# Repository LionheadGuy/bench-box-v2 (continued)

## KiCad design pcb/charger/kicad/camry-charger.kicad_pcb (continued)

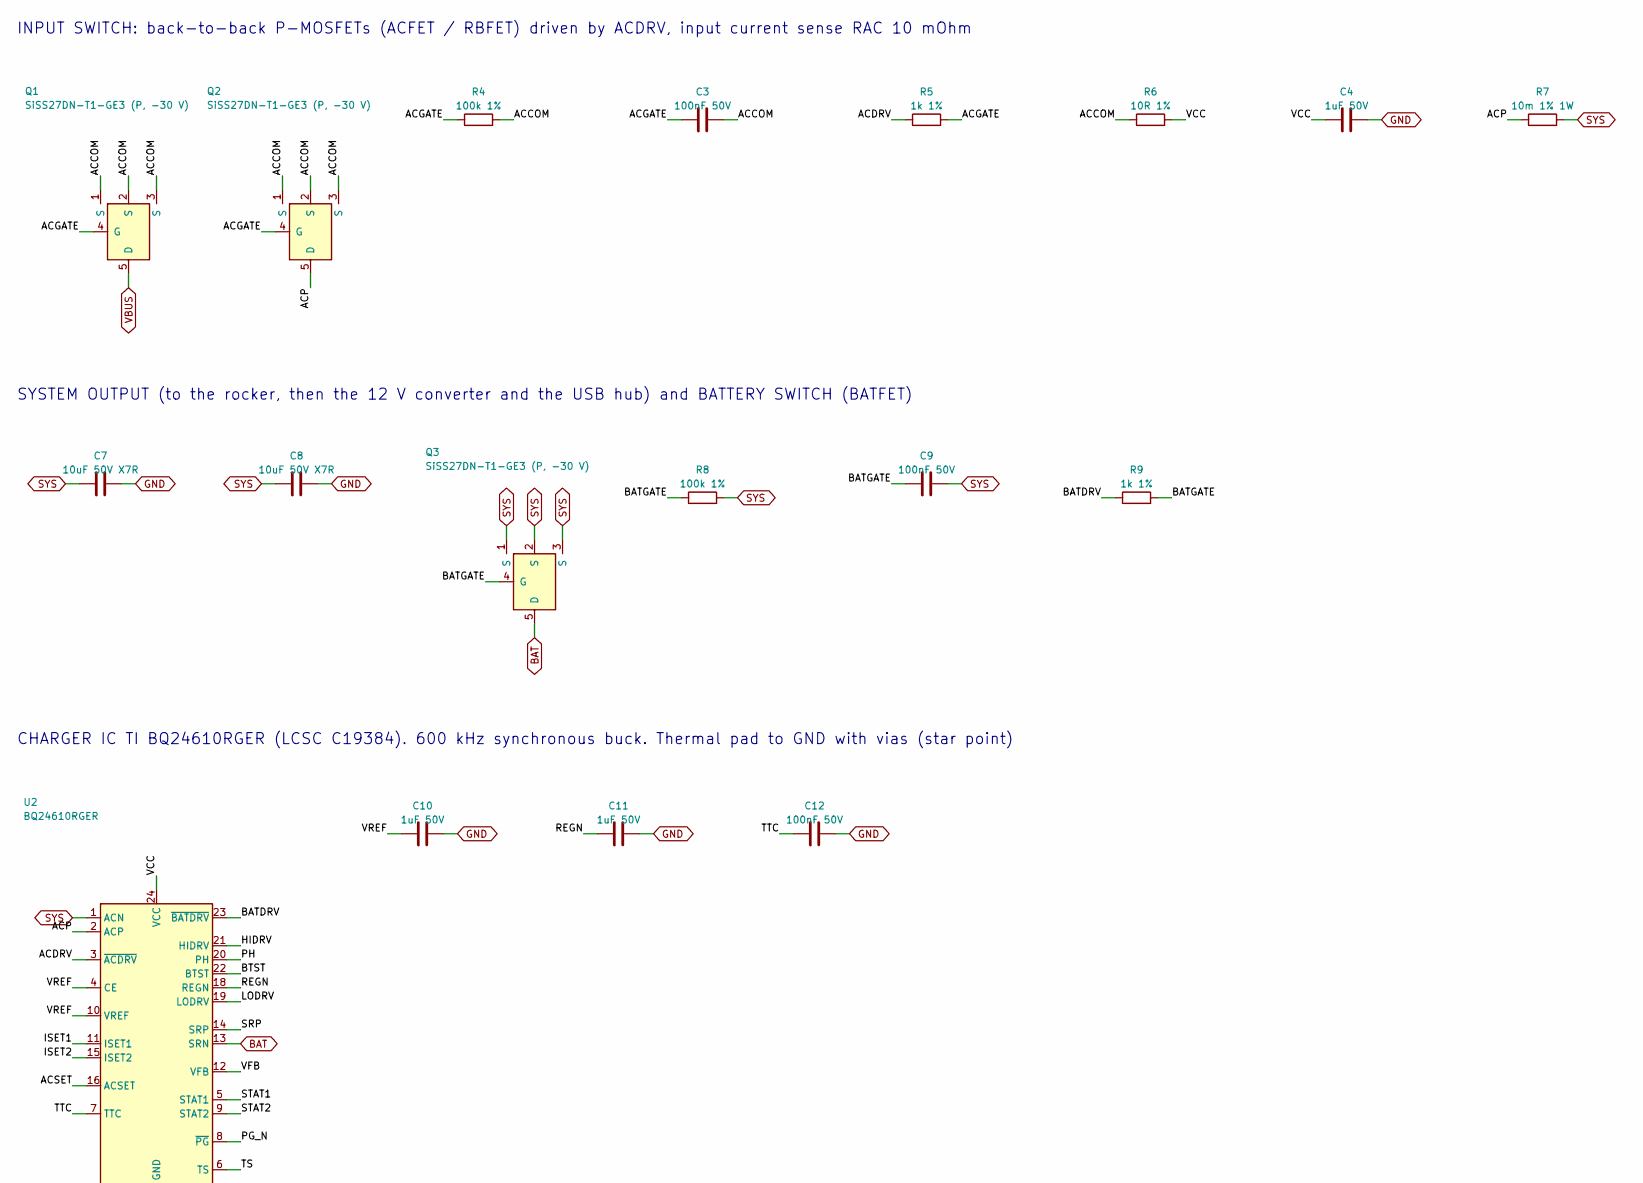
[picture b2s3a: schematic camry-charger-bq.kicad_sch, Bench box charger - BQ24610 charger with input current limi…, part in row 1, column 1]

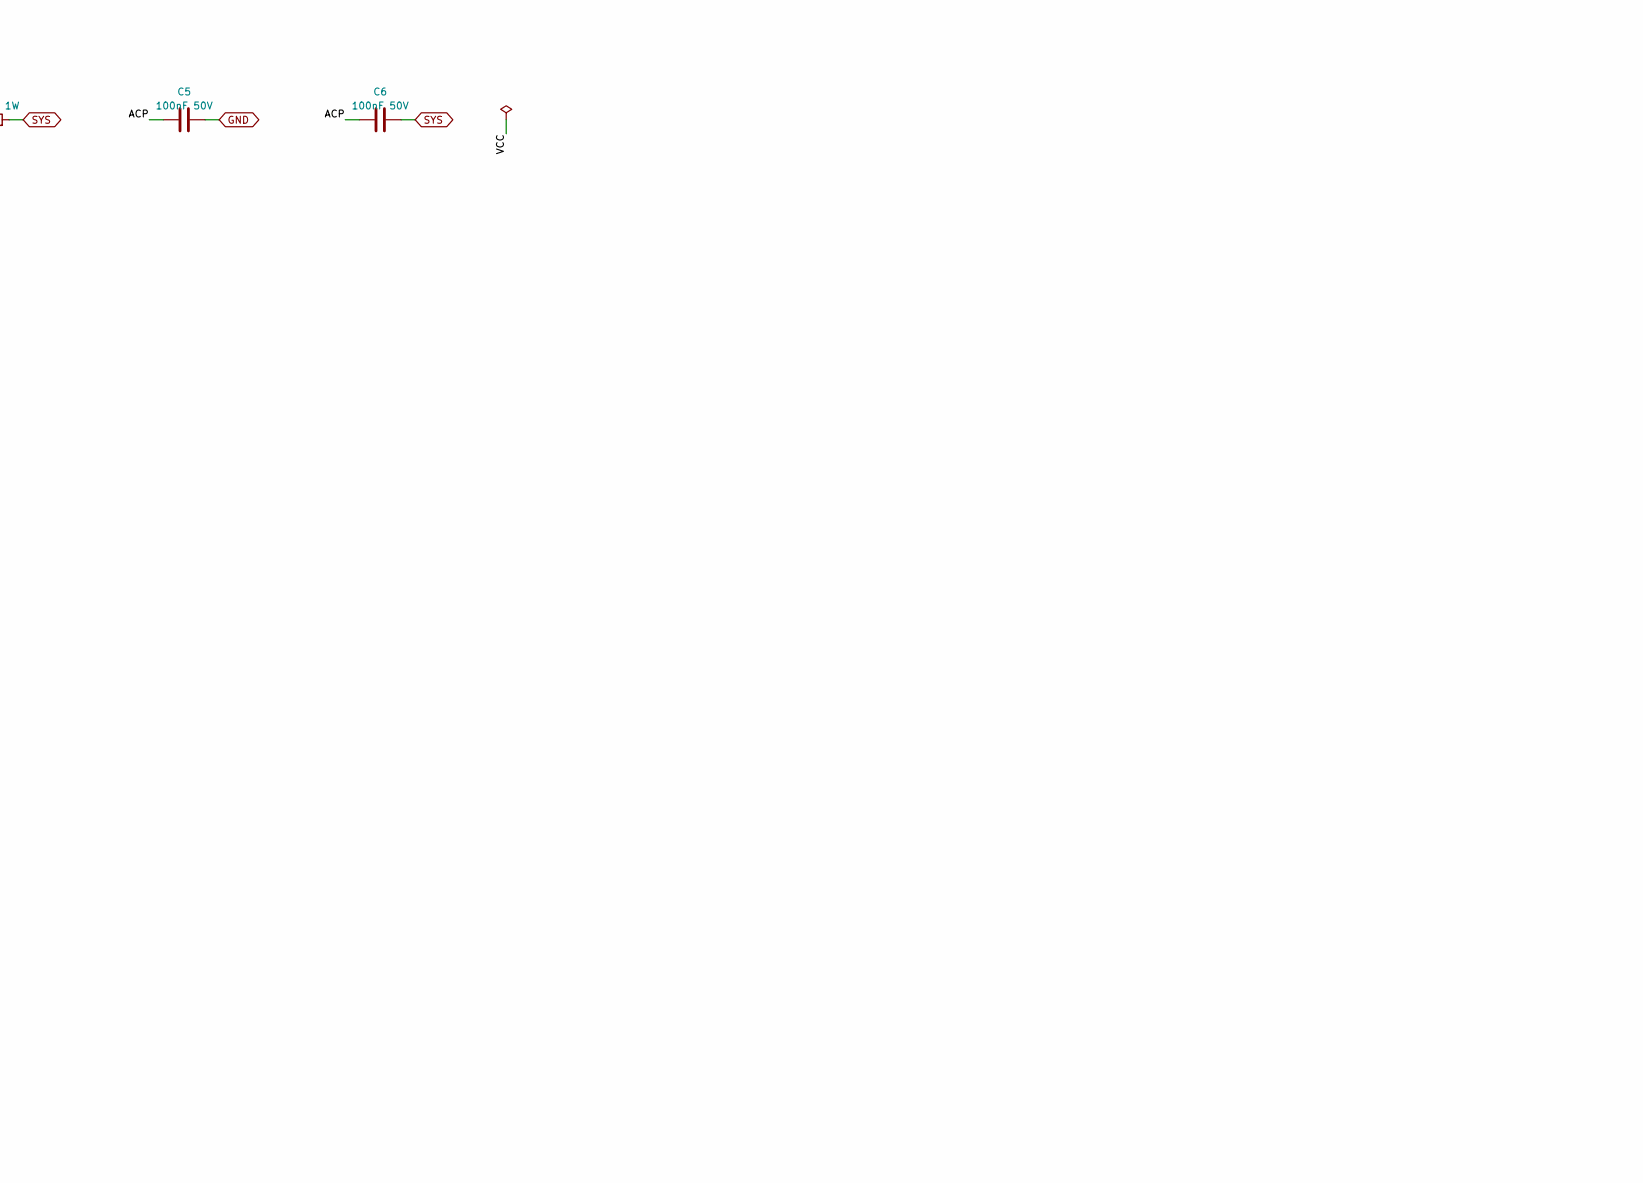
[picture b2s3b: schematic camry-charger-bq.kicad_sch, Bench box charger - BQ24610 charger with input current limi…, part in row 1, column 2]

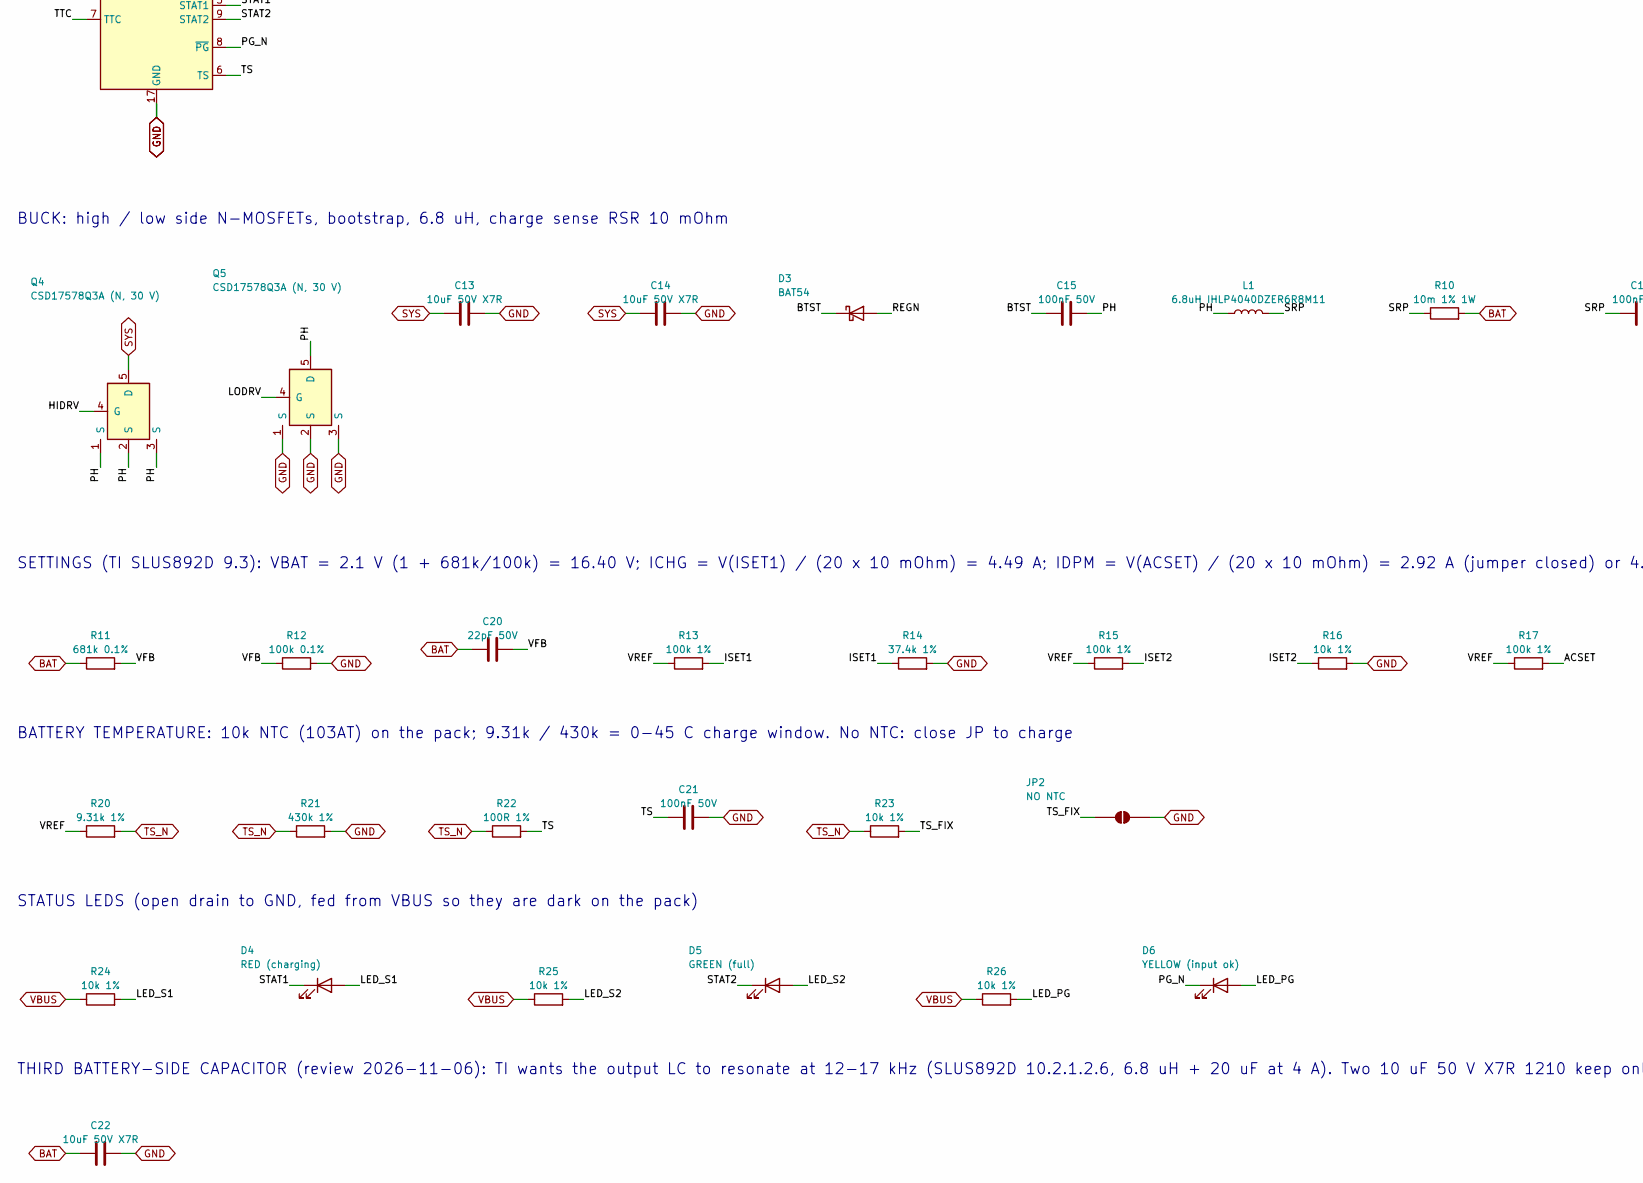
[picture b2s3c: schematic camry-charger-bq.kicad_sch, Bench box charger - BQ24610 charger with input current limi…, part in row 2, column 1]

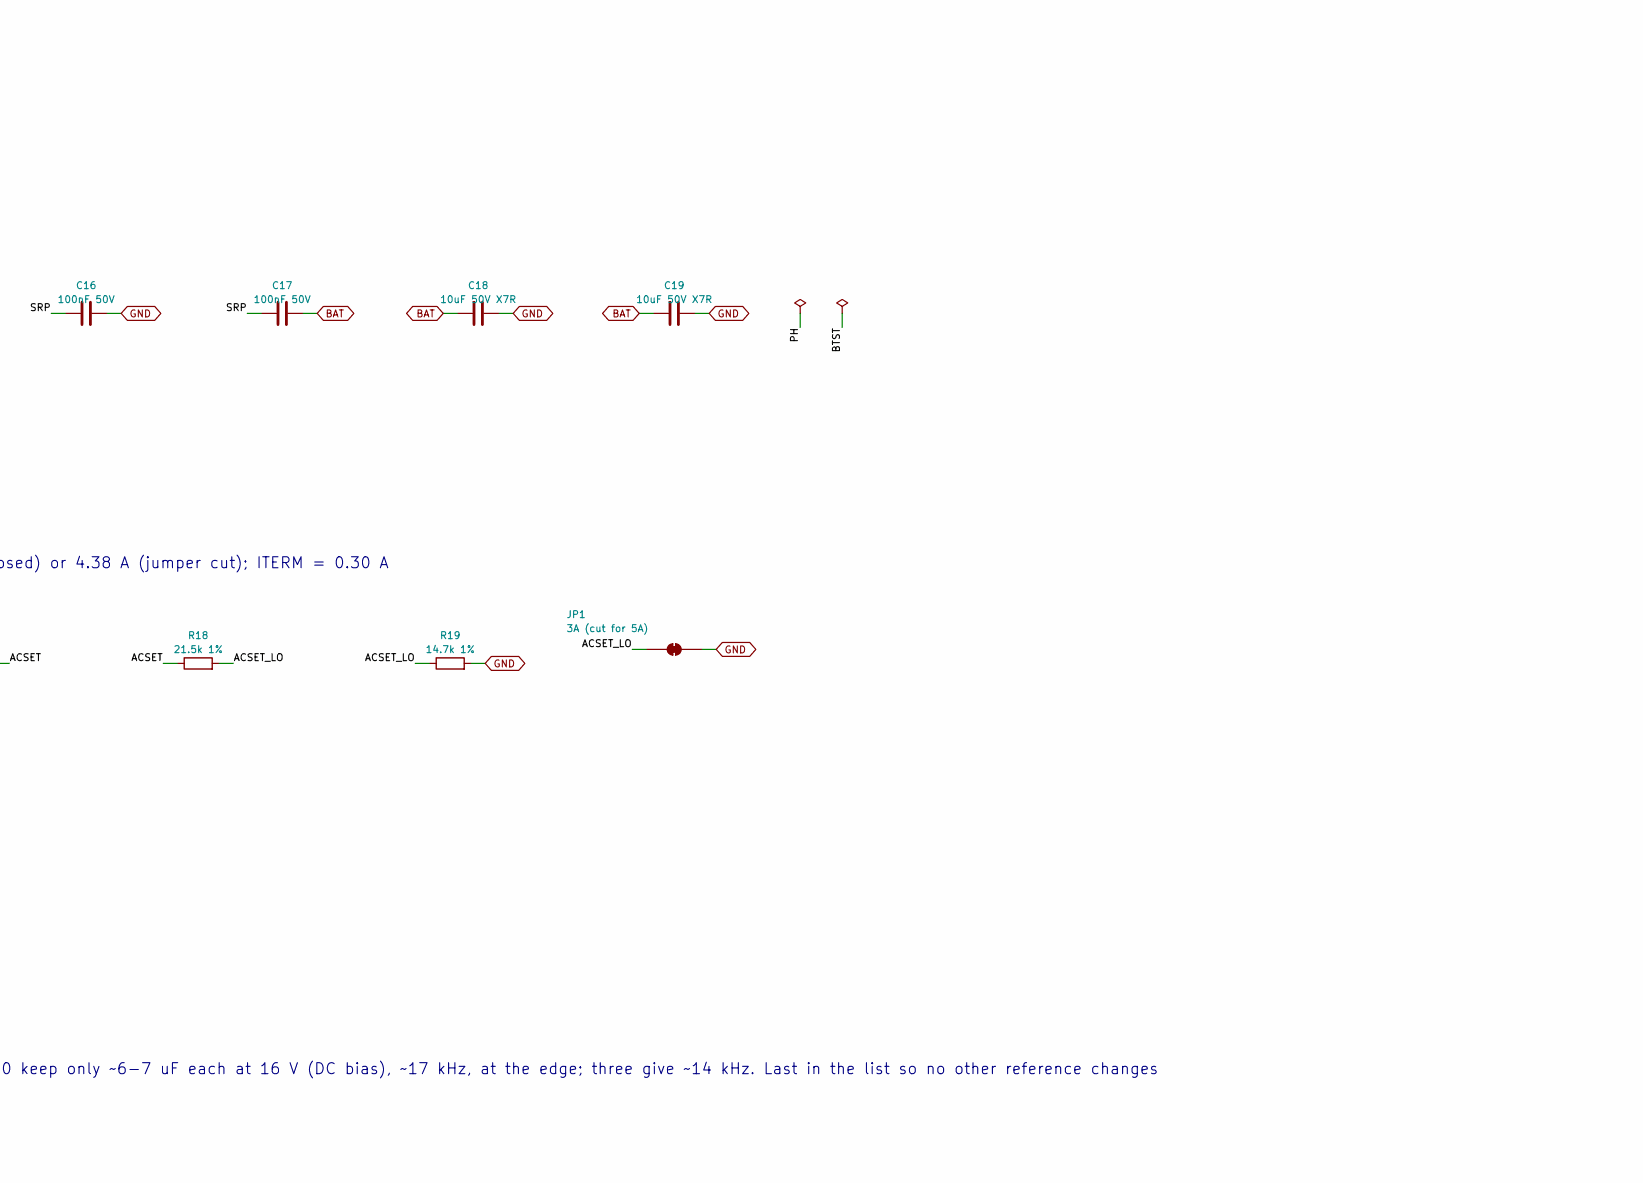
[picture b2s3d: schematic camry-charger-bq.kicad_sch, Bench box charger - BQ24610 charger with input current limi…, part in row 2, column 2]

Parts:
C3, C5, C6, C9, C12, C15, C16, C17, C21: 100nF 50V; C_0603_1608Metric; MPN GRM188R71H104KA93D
C4, C10, C11: 1uF 50V; C_0805_2012Metric; MPN GRM21BR71H105KA12L
C7, C8, C13, C14, C18, C19, C22: 10uF 50V X7R; C_1210_3225Metric; MPN GRM32ER71H106KA12L
C20: 22pF 50V; C_0603_1608Metric; MPN GRM1885C1H220JA01D
D3: BAT54; D_SOD-323; MPN BAT54WS-7-F
D4: RED (charging); LED_0603_1608Metric; MPN LTST-C191KRKT
D5: GREEN (full); LED_0603_1608Metric; MPN LTST-C191KGKT
D6: YELLOW (input ok); LED_0603_1608Metric; MPN LTST-C191KSKT
JP1: 3A (cut for 5A); SolderJumper-2_P1.3mm_Bridged_RoundedPad1.0x1.5mm
JP2: NO NTC; SolderJumper-2_P1.3mm_Open_RoundedPad1.0x1.5mm
L1: 6.8uH IHLP4040DZER6R8M11; L_Vishay_IHLP-4040; MPN IHLP4040DZER6R8M11
Q1, Q2, Q3: SiSS27DN-T1-GE3 (P, -30 V); Vishay_PowerPAK_1212-8_Single; MPN SISS27DN-T1-GE3
Q4, Q5: CSD17578Q3A (N, 30 V); VSON-8_3.3x3.3mm_P0.65mm_NexFET; MPN CSD17578Q3A; LCSC C205986
R4, R8, R13, R15, R17: 100k 1%; R_0603_1608Metric; MPN RC0603FR-07100KL
R5, R9: 1k 1%; R_0603_1608Metric; MPN RC0603FR-071KL
R6: 10R 1%; R_1206_3216Metric; MPN RC1206FR-0710RL
R7, R10: 10m 1% 1W; R_2512_6332Metric; MPN WSL2512R0100FEA
R11: 681k 0.1%; R_0603_1608Metric; MPN ERA-3AEB6813V
R12: 100k 0.1%; R_0603_1608Metric; MPN ERA-3AEB104V
R14: 37.4k 1%; R_0603_1608Metric; MPN RC0603FR-0737K4L
R16, R23, R24, R25, R26: 10k 1%; R_0603_1608Metric; MPN RC0603FR-0710KL
R18: 21.5k 1%; R_0603_1608Metric; MPN RC0603FR-0721K5L
R19: 14.7k 1%; R_0603_1608Metric; MPN RC0603FR-0714K7L
R20: 9.31k 1%; R_0603_1608Metric; MPN RC0603FR-079K31L
R21: 430k 1%; R_0603_1608Metric; MPN RC0603FR-07430KL
R22: 100R 1%; R_0603_1608Metric; MPN RC0603FR-07100RL
U2: BQ24610RGER; VQFN-24-1EP_4x4mm_P0.5mm_EP2.45x2.45mm_ThermalVias; MPN BQ24610RGER; LCSC C19384

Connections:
/BQ24610 charger with input current limiting and power path/ACCOM: C3.2, Q1.1 (S), Q1.2 (S), Q1.3 (S), Q2.1 (S), Q2.2 (S), Q2.3 (S), R4.2, R6.1
/BQ24610 charger with input current limiting and power path/ACDRV: R5.1, U2.3 (~ACDRV)
/BQ24610 charger with input current limiting and power path/ACGATE: C3.1, Q1.4 (G), Q2.4 (G), R4.1, R5.2
/BQ24610 charger with input current limiting and power path/ACP: C5.1, C6.1, Q2.5 (D), R7.1, U2.2 (ACP)
/BQ24610 charger with input current limiting and power path/ACSET: R17.2, R18.1, U2.16 (ACSET)
/BQ24610 charger with input current limiting and power path/ACSET_LO: JP1.1 (A), R18.2, R19.1
/BQ24610 charger with input current limiting and power path/BATDRV: R9.1, U2.23 (~BATDRV)
/BQ24610 charger with input current limiting and power path/BATGATE: C9.1, Q3.4 (G), R8.1, R9.2
/BQ24610 charger with input current limiting and power path/BTST: C15.1, D3.1 (K), U2.22 (BTST)
/BQ24610 charger with input current limiting and power path/HIDRV: Q4.4 (G), U2.21 (HIDRV)
/BQ24610 charger with input current limiting and power path/ISET1: R13.2, R14.1, U2.11 (ISET1)
/BQ24610 charger with input current limiting and power path/ISET2: R15.2, R16.1, U2.15 (ISET2)
/BQ24610 charger with input current limiting and power path/LED_PG: D6.2 (A), R26.2
/BQ24610 charger with input current limiting and power path/LED_S1: D4.2 (A), R24.2
/BQ24610 charger with input current limiting and power path/LED_S2: D5.2 (A), R25.2
/BQ24610 charger with input current limiting and power path/LODRV: Q5.4 (G), U2.19 (LODRV)
/BQ24610 charger with input current limiting and power path/PG_N: D6.1 (K), U2.8 (~PG)
/BQ24610 charger with input current limiting and power path/PH: C15.2, L1.1, Q4.1 (S), Q4.2 (S), Q4.3 (S), Q5.5 (D), U2.20 (PH)
/BQ24610 charger with input current limiting and power path/REGN: C11.1, D3.2 (A), U2.18 (REGN)
/BQ24610 charger with input current limiting and power path/SRP: C16.1, C17.1, L1.2, R10.1, U2.14 (SRP)
/BQ24610 charger with input current limiting and power path/STAT1: D4.1 (K), U2.5 (STAT1)
/BQ24610 charger with input current limiting and power path/STAT2: D5.1 (K), U2.9 (STAT2)
/BQ24610 charger with input current limiting and power path/TS: C21.1, R22.2, U2.6 (TS)
/BQ24610 charger with input current limiting and power path/TS_FIX: JP2.1 (A), R23.2
/BQ24610 charger with input current limiting and power path/TTC: C12.1, U2.7 (TTC)
/BQ24610 charger with input current limiting and power path/VCC: C4.1, R6.2, U2.24 (VCC)
/BQ24610 charger with input current limiting and power path/VFB: C20.2, R11.2, R12.1, U2.12 (VFB)
/BQ24610 charger with input current limiting and power path/VREF: C10.1, R13.1, R15.1, R17.1, R20.1, U2.4 (CE), U2.10 (VREF)
BAT: C17.2, C18.1, C19.1, C20.1, C22.1, Q3.5 (D), R10.2, R11.1, U2.13 (SRN); also elsewhere on the board
GND: C4.2, C5.2, C7.2, C8.2, C10.2, C11.2, C12.2, C13.2, C14.2, C16.2, C18.2, C19.2, C21.2, C22.2, JP1.2 (B), JP2.2 (B), Q5.1 (S), Q5.2 (S), Q5.3 (S), R12.2, R14.2, R16.2, R19.2, R21.2, U2.17 (GND), U2.25 (GND); also elsewhere on the board
SYS: C6.2, C7.1, C8.1, C9.2, C13.1, C14.1, Q3.1 (S), Q3.2 (S), Q3.3 (S), Q4.5 (D), R7.2, R8.2, U2.1 (ACN); also elsewhere on the board
TS_N: R20.2, R21.1, R22.1, R23.1; also elsewhere on the board
VBUS: Q1.5 (D), R24.1, R25.1, R26.1; also elsewhere on the board

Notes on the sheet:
INPUT SWITCH: back-to-back P-MOSFETs (ACFET / RBFET) driven by ACDRV, input current sense RAC 10 mOhm
SYSTEM OUTPUT (to the rocker, then the 12 V converter and the USB hub) and BATTERY SWITCH (BATFET)
CHARGER IC TI BQ24610RGER (LCSC C19384). 600 kHz synchronous buck. Thermal pad to GND with vias (star point)
BUCK: high / low side N-MOSFETs, bootstrap, 6.8 uH, charge sense RSR 10 mOhm
SETTINGS (TI SLUS892D 9.3): VBAT = 2.1 V (1 + 681k/100k) = 16.40 V; ICHG = V(ISET1) / (20 x 10 mOhm) = 4.49 A; IDPM = V(ACSET) / (20 x 10 mOhm) = 2.92 A (jumper closed) or 4.38 A (jumper cut); ITERM = 0.30 A
BATTERY TEMPERATURE: 10k NTC (103AT) on the pack; 9.31k / 430k = 0-45 C charge window. No NTC: close JP to charge
STATUS LEDS (open drain to GND, fed from VBUS so they are dark on the pack)
THIRD BATTERY-SIDE CAPACITOR (review 2026-11-06): TI wants the output LC to resonate at 12-17 kHz (SLUS892D 10.2.1.2.6, 6.8 uH + 20 uF at 4 A). Two 10 uF 50 V X7R 1210 keep only ~6-7 uF each at 16 V (DC bias), ~17 kHz, at the edge; three give ~14 kHz. Last in the list so no other reference changes

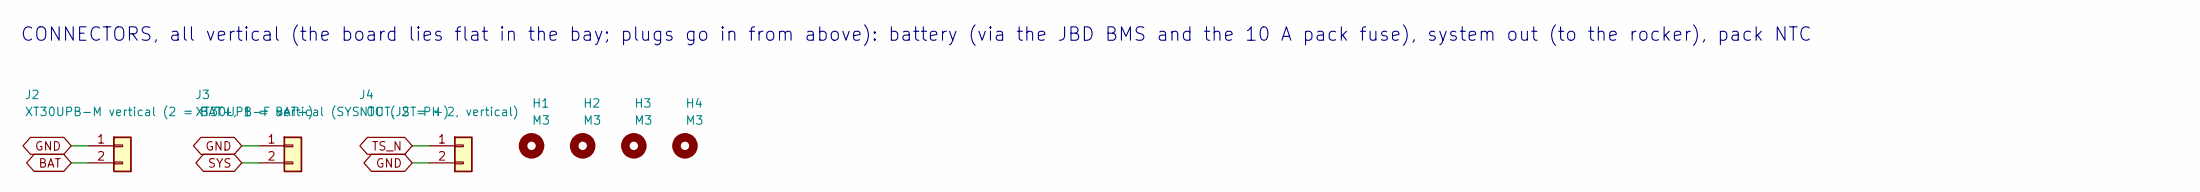
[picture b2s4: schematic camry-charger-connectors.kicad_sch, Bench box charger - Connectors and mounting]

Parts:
H1, H2, H3, H4: M3; MountingHole_3.2mm_M3
J2: XT30UPB-M vertical (2 = BAT+, 1 = BAT-); AMASS_XT30UPB-M_1x02_P5.0mm_Vertical; MPN XT30UPB-M; LCSC C428721
J3: XT30UPB-F vertical (SYS OUT, 2 = +); AMASS_XT30UPB-F_1x02_P5.0mm_Vertical; MPN XT30UPB-F; LCSC C108769
J4: NTC (JST PH 2, vertical); JST_PH_B2B-PH-K_1x02_P2.00mm_Vertical; MPN B2B-PH-K-S(LF)(SN)

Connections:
BAT: J2.2; also elsewhere on the board
GND: J2.1, J3.1, J4.2; also elsewhere on the board
SYS: J3.2; also elsewhere on the board
TS_N: J4.1; also elsewhere on the board

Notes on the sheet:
CONNECTORS, all vertical (the board lies flat in the bay; plugs go in from above): battery (via the JBD BMS and the 10 A pack fuse), system out (to the rocker), pack NTC

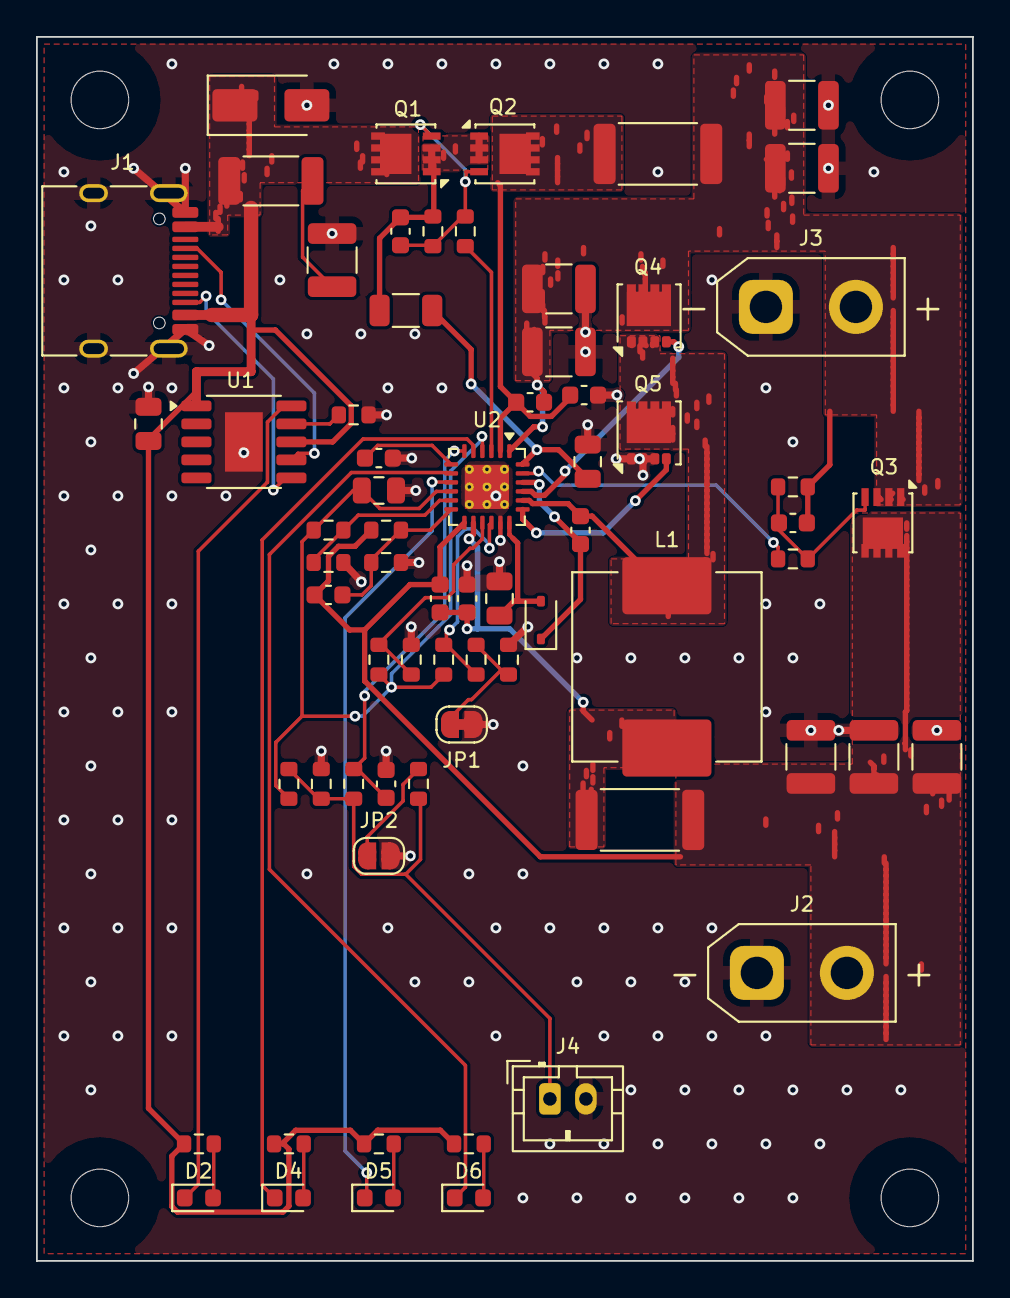
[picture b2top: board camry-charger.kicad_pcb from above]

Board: 4 copper layers, 52.0 x 68.0 mm, 72 parts (0 on the bottom side), 39 nets.

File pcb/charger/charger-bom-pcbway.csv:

Item,Qty,Designators,Manufacturer,MPN,LCSC,Description,Footprint,Type,Substitute
1,1,U1,WCH,CH224A,C42459160,"USB PD sink controller, ESSOP-10",SSOP-10-1EP_3.9x4.9mm_P1mm_EP2.1x3.3mm,SMD,exact part only
2,1,U2,Texas Instruments,BQ24610RGER,C19384,"battery charge controller, VQFN-24 4x4",VQFN-24-1EP_4x4mm_P0.5mm_EP2.45x2.45mm_ThermalVias,SMD,exact part only
3,3,Q1 Q2 Q3,Vishay Siliconix,SISS27DN-T1-GE3,,"P-MOSFET -30 V, PowerPAK 1212-8S",Vishay_PowerPAK_1212-8_Single,SMD,exact part only
4,2,Q4 Q5,Texas Instruments,CSD17578Q3A,C205986,"N-MOSFET 30 V, VSON-CLIP 3.3x3.3",VSON-8_3.3x3.3mm_P0.65mm_NexFET,SMD,exact part only
5,1,L1,Vishay Dale,IHLP4040DZER6R8M11,,"inductor 6.8 uH, Isat 7.5 A, 10.2 x 10.2 mm",L_Vishay_IHLP-4040,SMD,exact part only
6,1,D1,Littelfuse,SMAJ24A,,"TVS 24 V standoff, SMA",D_SMA,SMD,exact part only
7,2,D2 D5,Lite-On,LTST-C191KGKT,,"LED green, 0603",LED_0603_1608Metric,SMD,exact part only
8,1,D3,Diodes Incorporated,BAT54WS-7-F,,"Schottky 30 V 200 mA, SOD-323",D_SOD-323,SMD,exact part only
9,1,D4,Lite-On,LTST-C191KRKT,,"LED red, 0603",LED_0603_1608Metric,SMD,exact part only
10,1,D6,Lite-On,LTST-C191KSKT,,"LED yellow, 0603",LED_0603_1608Metric,SMD,exact part only
11,1,J1,Korean Hroparts Elec (HRO),TYPE-C-31-M-12,C165948,"USB-C receptacle 16P, 5 A 20 V",USB_C_Receptacle_HRO_TYPE-C-31-M-12,SMD,exact part only
12,1,J2,Changzhou Amass,XT30UPB-M,C428721,XT30 male PCB vertical (TME also stocks it),AMASS_XT30UPB-M_1x02_P5.0mm_Vertical,THT,exact part only
13,1,J3,Changzhou Amass,XT30UPB-F,C108769,XT30 female PCB vertical (TME also stocks it),AMASS_XT30UPB-F_1x02_P5.0mm_Vertical,THT,exact part only
14,1,J4,JST,B2B-PH-K-S(LF)(SN),,JST PH 2-pin vertical header,JST_PH_B2B-PH-K_1x02_P2.00mm_Vertical,THT,exact part only
15,1,C1,TDK,C3225X7R1H225K250AB,,2.2 uF 50 V X7R 1210,C_1210_3225Metric,SMD,equivalent OK
16,4,C2 C4 C10 C11,Murata,GRM21BR71H105KA12L,,1 uF 50 V X7R 0805,C_0805_2012Metric,SMD,equivalent OK
17,1,C20,Murata,GRM1885C1H220JA01D,,22 pF 50 V C0G 0603,C_0603_1608Metric,SMD,equivalent OK
18,9,C3 C5 C6 C9 C12 C15 C16 C17 C21,Murata,GRM188R71H104KA93D,,100 nF 50 V X7R 0603,C_0603_1608Metric,SMD,equivalent OK
19,7,C7 C8 C13 C14 C18 C19 C22,Murata,GRM32ER71H106KA12L,,10 uF 50 V X7R 1210,C_1210_3225Metric,SMD,equivalent OK
20,1,R1,Yageo,RC2010FK-072RL,,2 Ohm 1 % 2010,R_2010_5025Metric,SMD,equivalent OK
21,1,R11,Panasonic,ERA-3AEB6813V,,681 k 0.1 % 25 ppm 0603,R_0603_1608Metric,SMD,exact part only
22,1,R12,Panasonic,ERA-3AEB104V,,100 k 0.1 % 25 ppm 0603,R_0603_1608Metric,SMD,exact part only
23,1,R14,Yageo,RC0603FR-0737K4L,,37.4 k 1 % 0603,R_0603_1608Metric,SMD,equivalent OK
24,1,R18,Yageo,RC0603FR-0721K5L,,21.5 k 1 % 0603,R_0603_1608Metric,SMD,equivalent OK
25,1,R19,Yageo,RC0603FR-0714K7L,,14.7 k 1 % 0603,R_0603_1608Metric,SMD,equivalent OK
26,1,R2,Yageo,RC0603FR-07120KL,,120 k 1 % 0603,R_0603_1608Metric,SMD,equivalent OK
27,1,R20,Yageo,RC0603FR-079K31L,,9.31 k 1 % 0603,R_0603_1608Metric,SMD,equivalent OK
28,1,R21,Yageo,RC0603FR-07430KL,,430 k 1 % 0603,R_0603_1608Metric,SMD,equivalent OK
29,1,R22,Yageo,RC0603FR-07100RL,,100 Ohm 1 % 0603,R_0603_1608Metric,SMD,equivalent OK
30,6,R3 R16 R23 R24 R25 R26,Yageo,RC0603FR-0710KL,,10 k 1 % 0603,R_0603_1608Metric,SMD,equivalent OK
31,5,R4 R8 R13 R15 R17,Yageo,RC0603FR-07100KL,,100 k 1 % 0603,R_0603_1608Metric,SMD,equivalent OK
32,2,R5 R9,Yageo,RC0603FR-071KL,,1 k 1 % 0603,R_0603_1608Metric,SMD,equivalent OK
33,1,R6,Yageo,RC1206FR-0710RL,,10 Ohm 1 % 1206,R_1206_3216Metric,SMD,equivalent OK
34,2,R7 R10,Vishay Dale,WSL2512R0100FEA,,10 mOhm 1 % 1 W 2512 current sense,R_2512_6332Metric,SMD,exact part only

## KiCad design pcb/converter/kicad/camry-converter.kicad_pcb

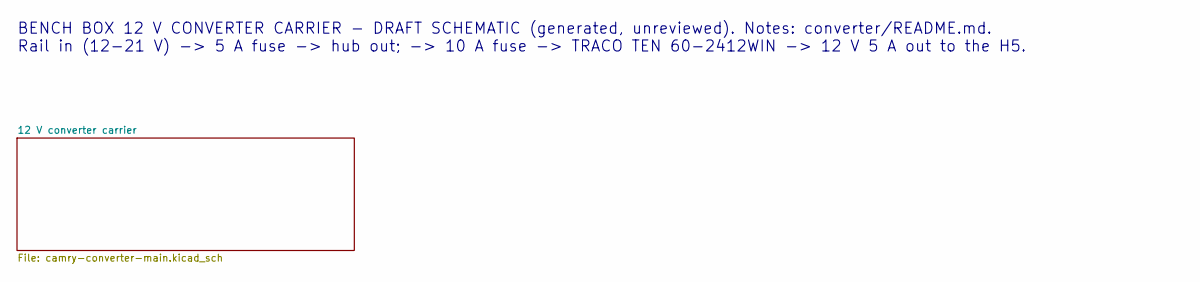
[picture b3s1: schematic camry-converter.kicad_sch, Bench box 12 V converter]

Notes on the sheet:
BENCH BOX 12 V CONVERTER CARRIER - DRAFT SCHEMATIC (generated, unreviewed). Notes: converter/README.md. Rail in (12-21 V) -> 5 A fuse -> hub out; -> 10 A fuse -> TRACO TEN 60-2412WIN -> 12 V 5 A out to the H5.

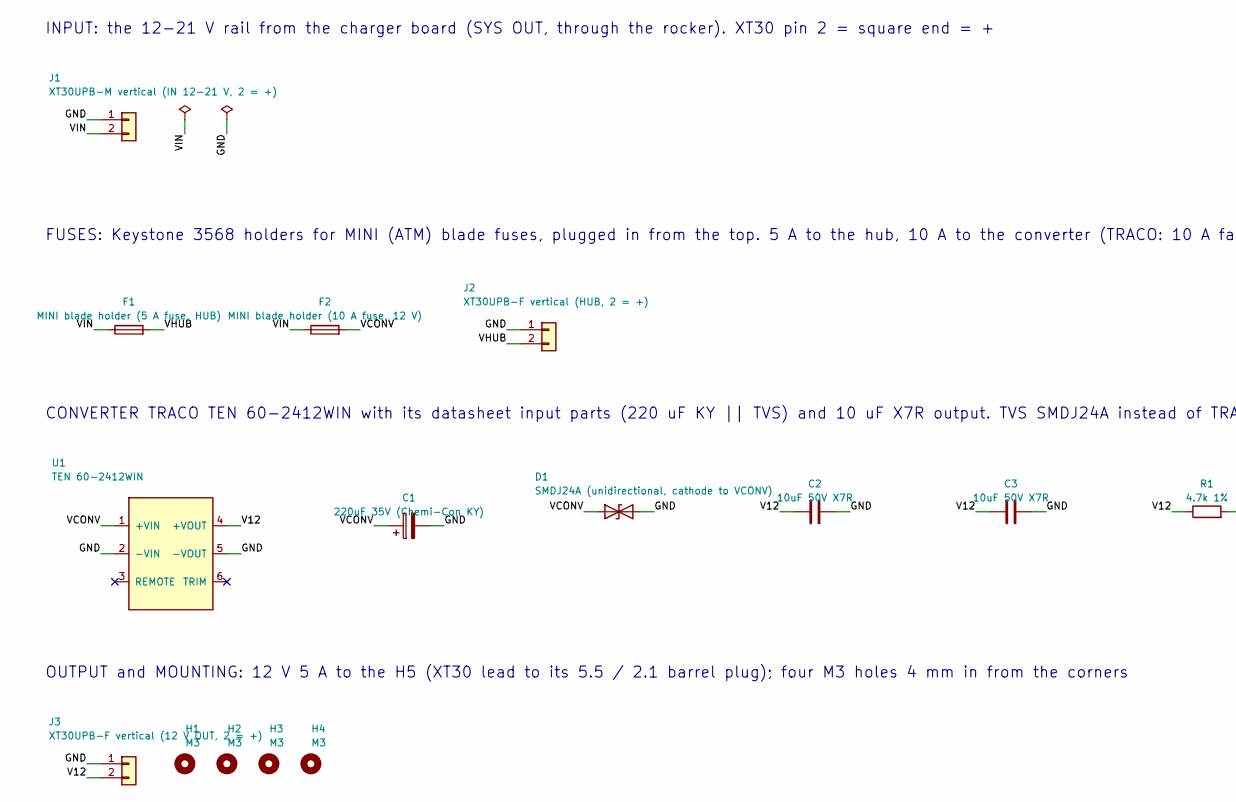
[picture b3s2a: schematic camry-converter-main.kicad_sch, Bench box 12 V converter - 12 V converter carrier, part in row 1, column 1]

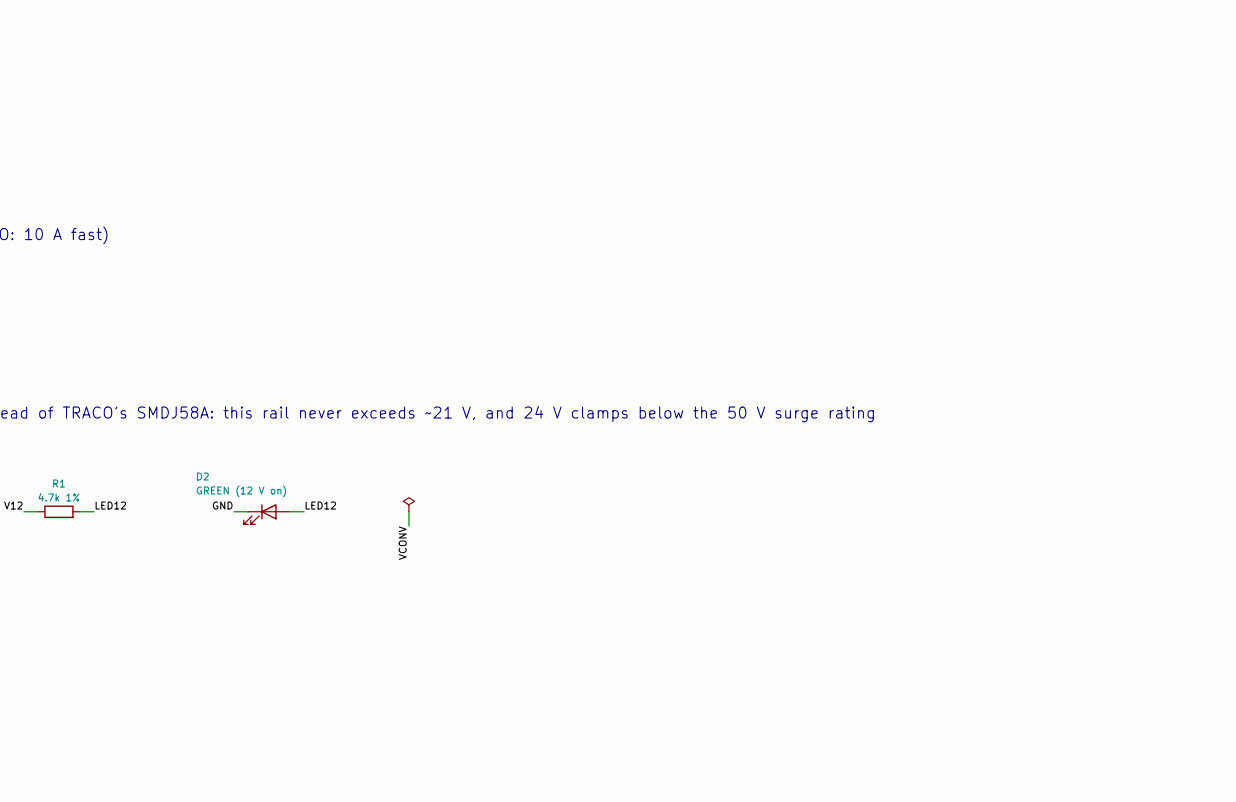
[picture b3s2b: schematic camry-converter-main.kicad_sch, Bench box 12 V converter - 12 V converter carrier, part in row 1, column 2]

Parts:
C1: 220uF 35V (Chemi-Con KY); CP_Radial_D10.0mm_P5.00mm; MPN EKY-350ELL221MJC5S
C2, C3: 10uF 50V X7R; C_1210_3225Metric; MPN GRM32ER71H106KA12L
D1: SMDJ24A (unidirectional, cathode to VCONV); D_SMC; MPN SMDJ24A
D2: GREEN (12 V on); LED_0603_1608Metric; MPN LTST-C191KGKT
F1: MINI blade holder (5 A fuse, HUB); Fuseholder_Blade_Mini_Keystone_3568; MPN 3568
F2: MINI blade holder (10 A fuse, 12 V); Fuseholder_Blade_Mini_Keystone_3568; MPN 3568
H1, H2, H3, H4: M3; MountingHole_3.2mm_M3
J1: XT30UPB-M vertical (IN 12-21 V, 2 = +); AMASS_XT30UPB-M_1x02_P5.0mm_Vertical; MPN XT30UPB-M; LCSC C428721
J2: XT30UPB-F vertical (HUB, 2 = +); AMASS_XT30UPB-F_1x02_P5.0mm_Vertical; MPN XT30UPB-F; LCSC C108769
J3: XT30UPB-F vertical (12 V OUT, 2 = +); AMASS_XT30UPB-F_1x02_P5.0mm_Vertical; MPN XT30UPB-F; LCSC C108769
R1: 4.7k 1%; R_0603_1608Metric; MPN RC0603FR-074K7L
U1: TEN 60-2412WIN; TRACO_TEN60WIN_THT; MPN TEN 60-2412WIN

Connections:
/12 V converter carrier/GND: C1.2, C2.2, C3.2, D1.2 (A2), D2.1 (K), J1.1, J2.1, J3.1, U1.2 (-VIN), U1.5 (-VOUT)
/12 V converter carrier/LED12: D2.2 (A), R1.2
/12 V converter carrier/V12: C2.1, C3.1, J3.2, R1.1, U1.4 (+VOUT)
/12 V converter carrier/VCONV: C1.1, D1.1 (A1), F2.2, U1.1 (+VIN)
/12 V converter carrier/VHUB: F1.2, J2.2
/12 V converter carrier/VIN: F1.1, F2.1, J1.2

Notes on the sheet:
INPUT: the 12-21 V rail from the charger board (SYS OUT, through the rocker). XT30 pin 2 = square end = +
FUSES: Keystone 3568 holders for MINI (ATM) blade fuses, plugged in from the top. 5 A to the hub, 10 A to the converter (TRACO: 10 A fast)
CONVERTER TRACO TEN 60-2412WIN with its datasheet input parts (220 uF KY || TVS) and 10 uF X7R output. TVS SMDJ24A instead of TRACO's SMDJ58A: this rail never exceeds ~21 V, and 24 V clamps below the 50 V surge rating
OUTPUT and MOUNTING: 12 V 5 A to the H5 (XT30 lead to its 5.5 / 2.1 barrel plug); four M3 holes 4 mm in from the corners

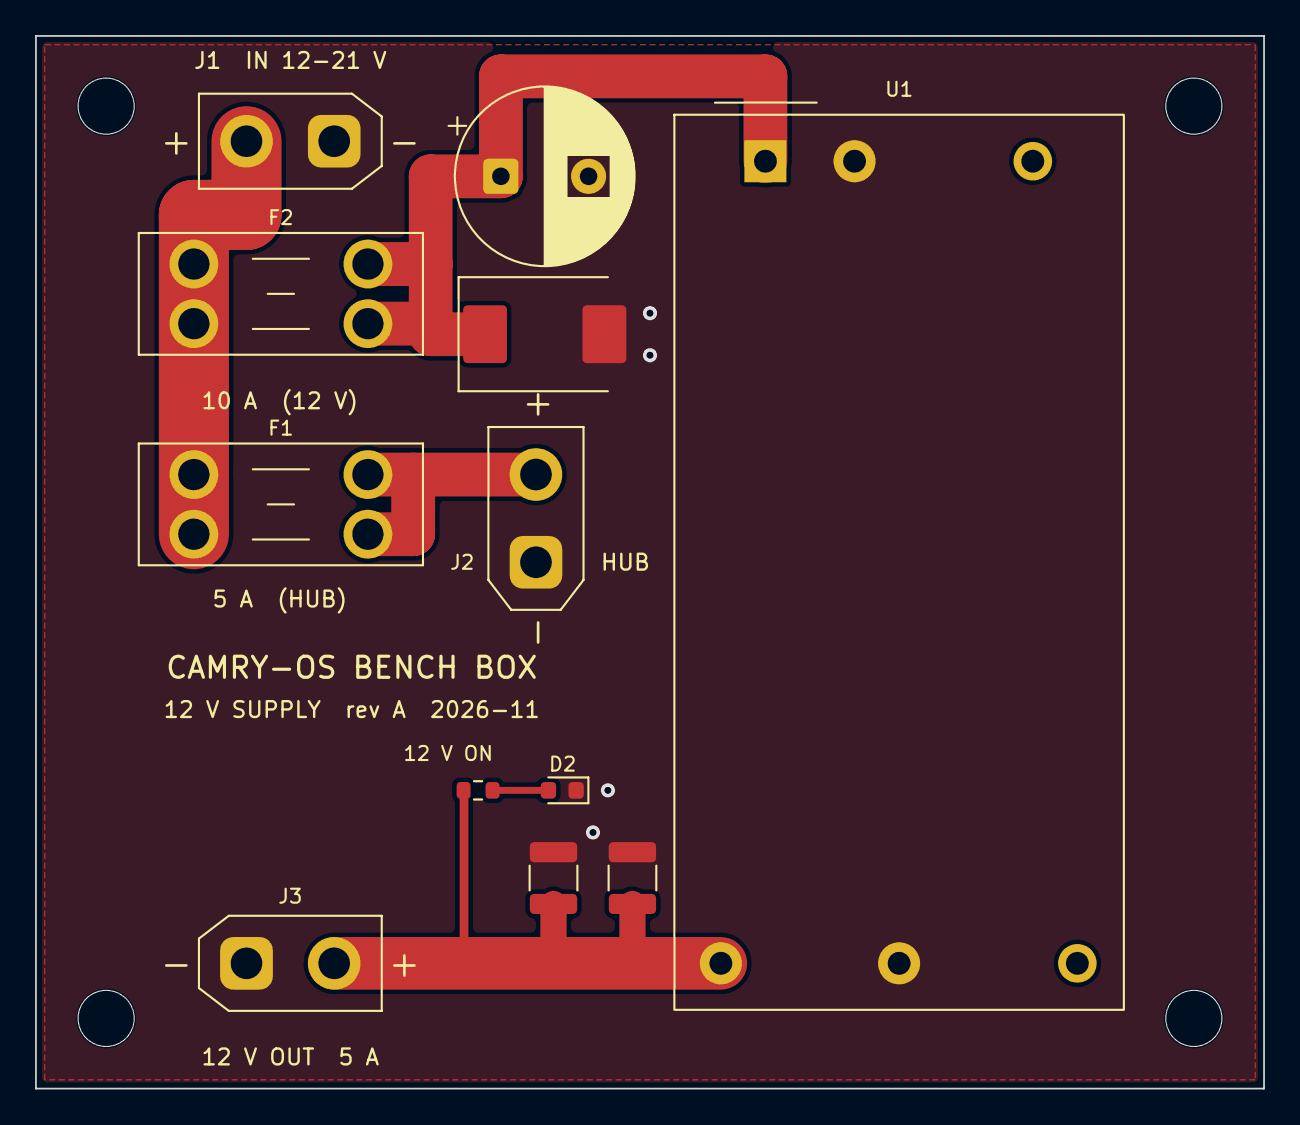
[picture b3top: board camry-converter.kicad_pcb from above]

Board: 2 copper layers, 70.0 x 60.0 mm, 16 parts (0 on the bottom side), 6 nets.

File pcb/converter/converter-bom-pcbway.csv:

Item,Qty,Designators,Manufacturer,MPN,LCSC,Description,Footprint,Type,Substitute
1,1,U1,TRACO Power,TEN 60-2412WIN,,"DC/DC 9-36 V in, 12 V 5 A, 2 x 1 in THT",TRACO_TEN60WIN_THT,THT,exact part only
2,2,F1 F2,Keystone Electronics,3568,,"MINI blade fuse holder, THT, 30 A",Fuseholder_Blade_Mini_Keystone_3568,THT,exact part only
3,1,D1,Littelfuse,SMDJ24A,,"TVS 24 V standoff, 3 kW, DO-214AB",D_SMC,SMD,exact part only
4,1,D2,Lite-On,LTST-C191KGKT,,"LED green, 0603",LED_0603_1608Metric,SMD,exact part only
5,1,J1,Changzhou Amass,XT30UPB-M,C428721,XT30 male PCB vertical,AMASS_XT30UPB-M_1x02_P5.0mm_Vertical,THT,exact part only
6,2,J2 J3,Changzhou Amass,XT30UPB-F,C108769,XT30 female PCB vertical,AMASS_XT30UPB-F_1x02_P5.0mm_Vertical,THT,exact part only
7,1,C1,Chemi-Con,EKY-350ELL221MJC5S,,"220 uF 35 V aluminium electrolytic, 10 mm, 5 mm pitch",CP_Radial_D10.0mm_P5.00mm,THT,equivalent OK
8,2,C2 C3,Murata,GRM32ER71H106KA12L,,10 uF 50 V X7R 1210,C_1210_3225Metric,SMD,equivalent OK
9,1,R1,Yageo,RC0603FR-074K7L,,4.7 k 1 % 0603,R_0603_1608Metric,SMD,equivalent OK
